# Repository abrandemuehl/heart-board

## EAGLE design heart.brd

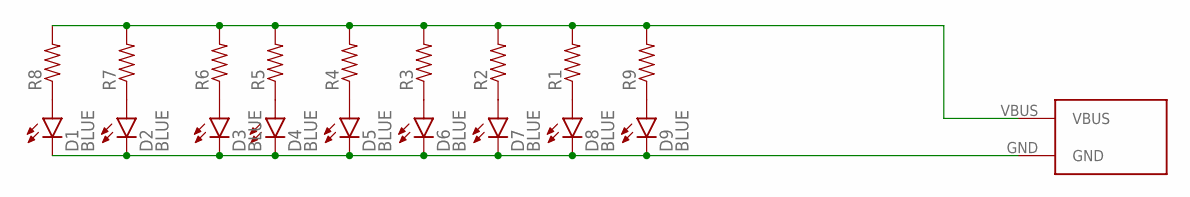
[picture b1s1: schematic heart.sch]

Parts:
D1, D2, D3, D4, D5, D6, D7, D8, D9: BLUE; LED-0603
R1, R2, R3, R4, R5, R6, R7, R8, R9: RESISTOR0603-RES; 0603-RES
U$1: USBMALEA

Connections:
5V: R1.2, R2.2, R3.2, R4.2, R5.2, R6.2, R7.2, R8.2, R9.2, U$1.VBUS
GND: D1.C, D2.C, D3.C, D4.C, D5.C, D6.C, D7.C, D8.C, D9.C, U$1.GND
unnamed: D8.A, R1.1
unnamed: D7.A, R2.1
unnamed: D6.A, R3.1
unnamed: D5.A, R4.1
unnamed: D4.A, R5.1
unnamed: D3.A, R6.1
unnamed: D2.A, R7.1
unnamed: D1.A, R8.1
unnamed: D9.A, R9.1

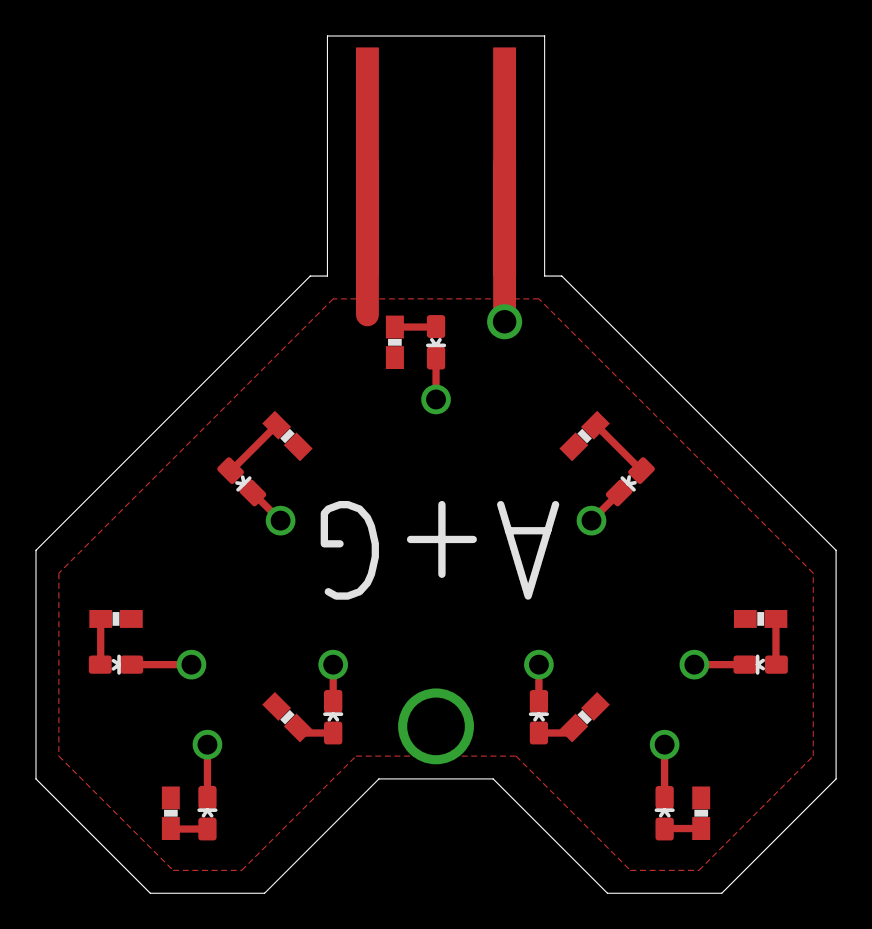
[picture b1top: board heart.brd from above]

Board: 2 copper layers, 44.5 x 47.6 mm, 19 parts (0 on the bottom side), 11 nets.

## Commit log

2017-02-10 Shipped board

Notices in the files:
parts and their libraries:
SparkFun-LED: Licensing: Creative Commons ShareAlike 4.0 International - https://creativecommons.org/licenses/by-sa/4.0
